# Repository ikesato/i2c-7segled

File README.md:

概要
====

- I2C を使用した7セグメントLED表示器です
- おもに Raspberry PI からの利用を想定してます  
 Raspberry PI からシェルコマンドを利用して直接制御可能
- 点滅、スクロール機能
- 最大で８つのページ切り替え機能

### パーツ

- PIC18F14K50 (SOIC)  
 1.25mm ピッチ

- TD62083 (SOIC)  
 1.25mm ピッチ

- ダイナミック接続４桁高輝度赤色７セグメントＬＥＤ表示器　カソードコモン　カソード共通接続  
 http://akizukidenshi.com/catalog/g/gI-03955/

- チップ抵抗  
 270Ω  1/4W x 8  

- チップコンデンサ  
 0.1uF  x2

### I2C通信仕様

- 通信速度 100kHz
- I2C スレーブ
- ライト要求 (Master -> Slaveへのライト要求) のみ

### コマンド

| address | data   | description |
|---------|--------|-------------|
| 0x00    | なし   | リセット    |
| 0x01    | なし   | LCD消灯     |
| 0x02    | 1..8   | 最大ページ数設定  |
| 0x03    | 0..255 | スクロール速度設定 (0.1秒 * (指定値+1)) *1  |
| 0x04    | 0..255 | ページ切り替え速度設定 (0.1秒 * (指定値+1))  |
| 0x05    | 0..255 | 点滅速度設定 (0.1秒 * (指定値+1))  |
| 0x06    | 0..1   | スクロール設定 (0:disable 1:enable)|
| 0x07    | 0..1   | 点滅設定 (0:disable 1:enable) |
| 0x10    | 0..7   | カレントページ設定 *2 |
| 0x11    | 文字列 | 描画文字列を指定、終端は 0x00 を指定します *3 |

*1 ... 文字のスクロール速度になります。例えば 19 を指定した場合 0.1*(19+1) で2秒単位にスクロールします。  
*2 ... 0 から数えるページ数を指定します。範囲は 0 から 最大ページ数-1 になります。  
*3 ... 描画文字列は ASCII コードで指定します。表示可能文字は数字、スペース、ハイフン、アンダースコア、パイプ、アルファベット（大文字、小文字）、ピリオドです。  

### 回路図

[EAGLE ファイル](./doc/eagle/i2c-7segled-SOIC.sch)

### ボード

[EAGLE ファイル](./doc/eagle/i2c-7segled-SOIC.brd)

### Unix シェルでの使用方法

shell ディレクトリにあるシェルコマンド利用することで簡単に LED を制御できます。

|コマンド              |引数  |説明                   |
|----------------------|------|-----------------------|
|7seg_clear            |なし  |7seg LCD をクリアします|
|7seg_enable_blink     |0..1  |点滅設定 (0:disable 1:enable)|
|7seg_enable_scroll    |0..1  |スクロール設定 (0:disable 1:enable)|
|7seg_puts             |文字列|描画文字列を指定|
|7seg_puts_from_stdin  |なし  |文字列を標準入力からリードして描画します。CTRL-C で中断するまで続けます。|
|7seg_reset            |なし  |リセット、内部変数ふくめ全て初期化します|
|7seg_set_blink_speed  |0..255| 点滅速度設定 (0.1秒 * (指定値+1))  |
|7seg_set_current_page |0..7  | カレントページ設定 |
|7seg_set_flip_speed   |0..255| ページ切り替え速度設定 (0.1秒 * (指定値+1))  |
|7seg_set_page_num     |1..8  | 最大ページ数設定  |
|7seg_set_scroll_speed |0..255| スクロール速度設定 (0.1秒 * (指定値+1))  |

例
```````````````````
cd shell
./7seg_reset
./7seg_enable_scroll 1
./7seg_set_scroll_speed 10
./7seg_puts "HELLO"
```````````````````

### 仕様

| 機能               | 仕様  |
|--------------------|--------------|
|インターフェース    |I2Cスレーブ   |
|I2Cスレーブアドレス|0x70         |
|I2C転送速度         |100kHz        |
|最大表示文字数      |終端NULL含めて200文字。複数ページの場合は各ページの終端NULL含めて合計で200文字|
|使用可能文字        |ASCII コードでスペース、ハイフン、アンダースコア、パイプ、アルファベット（大文字、小文字）、ピリオド|
|最大ページ数        |8ページ|
|表示機能            |ページ切り替え、文字スクロール、点滅、クリア|

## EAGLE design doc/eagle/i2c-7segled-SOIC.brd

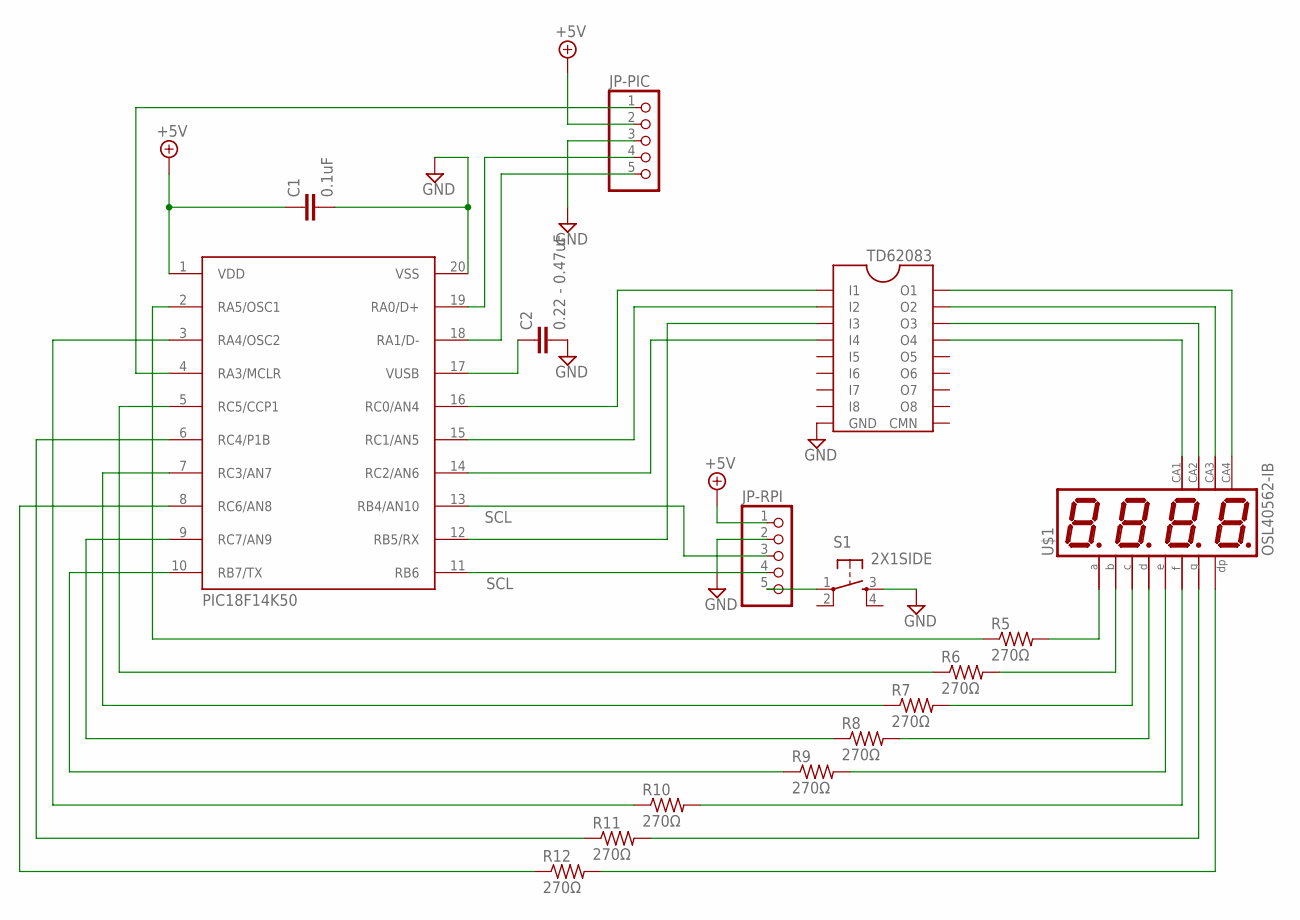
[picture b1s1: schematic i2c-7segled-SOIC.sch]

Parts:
C1: 0.1uF; C0504
C2: 0.22 - 0.47uF; C0504
JP-PIC: PINHD-1X5; 1X05
JP-RPI: PINHD-1X5; 1X05
PIC18F14K50: PIC18F14K50-SO; SO20
R5, R6, R7, R8, R9, R10, R11, R12: 270Ω; M0805
S1: 2X1SIDE
U$1: OSL40562-IB; OSL40562
U$2: TD62083; SO18

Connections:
+5V: C1.1, JP-PIC.2, JP-RPI.1, PIC18F14K50.1 (VDD)
GND: C1.2, C2.2, JP-PIC.3, JP-RPI.2, PIC18F14K50.20 (VSS), S1.3 (S), U$2.9 (GND)
unnamed: U$1.6 (CA), U$2.18 (O1)
unnamed: C2.1, PIC18F14K50.17 (VUSB)
unnamed: PIC18F14K50.12 (RB5/RX), U$2.3 (I3)
unnamed: JP-RPI.5, S1.1
unnamed: PIC18F14K50.14 (RC2/AN6), U$2.4 (I4)
unnamed: PIC18F14K50.15 (RC1/AN5), U$2.2 (I2)
unnamed: PIC18F14K50.16 (RC0/AN4), U$2.1 (I1)
unnamed: U$1.9 (CA), U$2.16 (O3)
unnamed: U$1.8 (CA), U$2.17 (O2)
unnamed: U$1.12 (CA), U$2.15 (O4)
unnamed: PIC18F14K50.2 (RA5/OSC1), R5.1
unnamed: R5.2, U$1.11 (A)
unnamed: PIC18F14K50.5 (RC5/CCP1), R6.1
unnamed: PIC18F14K50.7 (RC3/AN7), R7.1
unnamed: PIC18F14K50.9 (RC7/AN9), R8.1
unnamed: PIC18F14K50.10 (RB7/TX), R9.1
unnamed: PIC18F14K50.3 (RA4/OSC2), R10.1
unnamed: PIC18F14K50.6 (RC4/P1B), R11.1
unnamed: PIC18F14K50.8 (RC6/AN8), R12.1
unnamed: R6.2, U$1.7 (B)
unnamed: R7.2, U$1.4 (C)
unnamed: R8.2, U$1.2 (D)
unnamed: R9.2, U$1.1 (E)
unnamed: R10.2, U$1.10 (F)
unnamed: R11.2, U$1.5 (G)
unnamed: R12.2, U$1.3 (DP)
unnamed: JP-PIC.1, PIC18F14K50.4 (RA3/MCLR)
unnamed: JP-PIC.4, PIC18F14K50.19 (RA0/D+)
unnamed: JP-PIC.5, PIC18F14K50.18 (RA1/D-)
unnamed: JP-RPI.4, PIC18F14K50.11 (RB6)
SCL: JP-RPI.3, PIC18F14K50.13 (RB4/AN10)

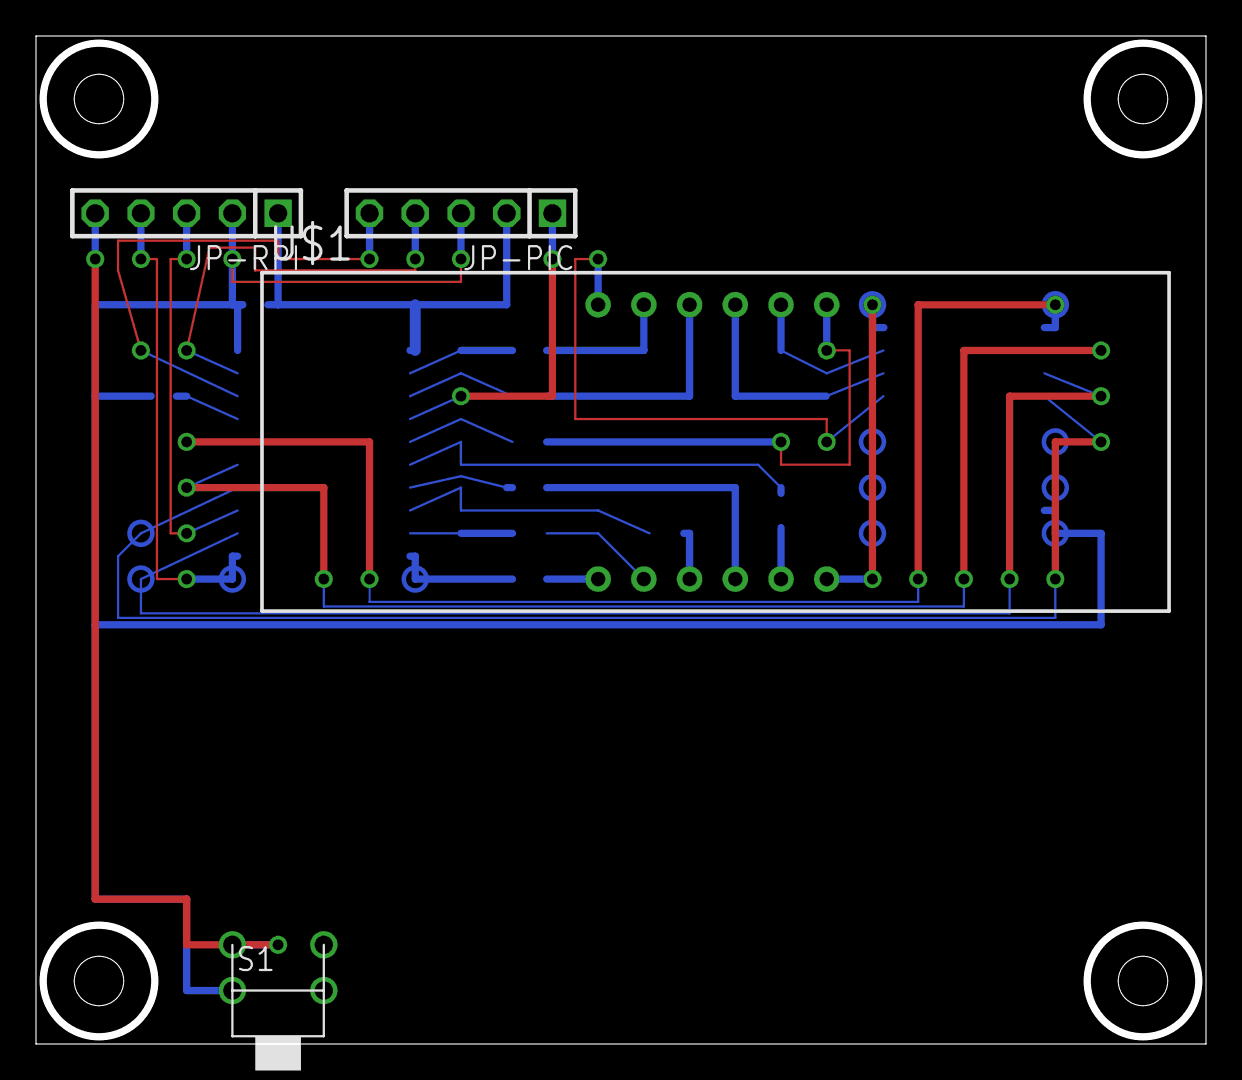
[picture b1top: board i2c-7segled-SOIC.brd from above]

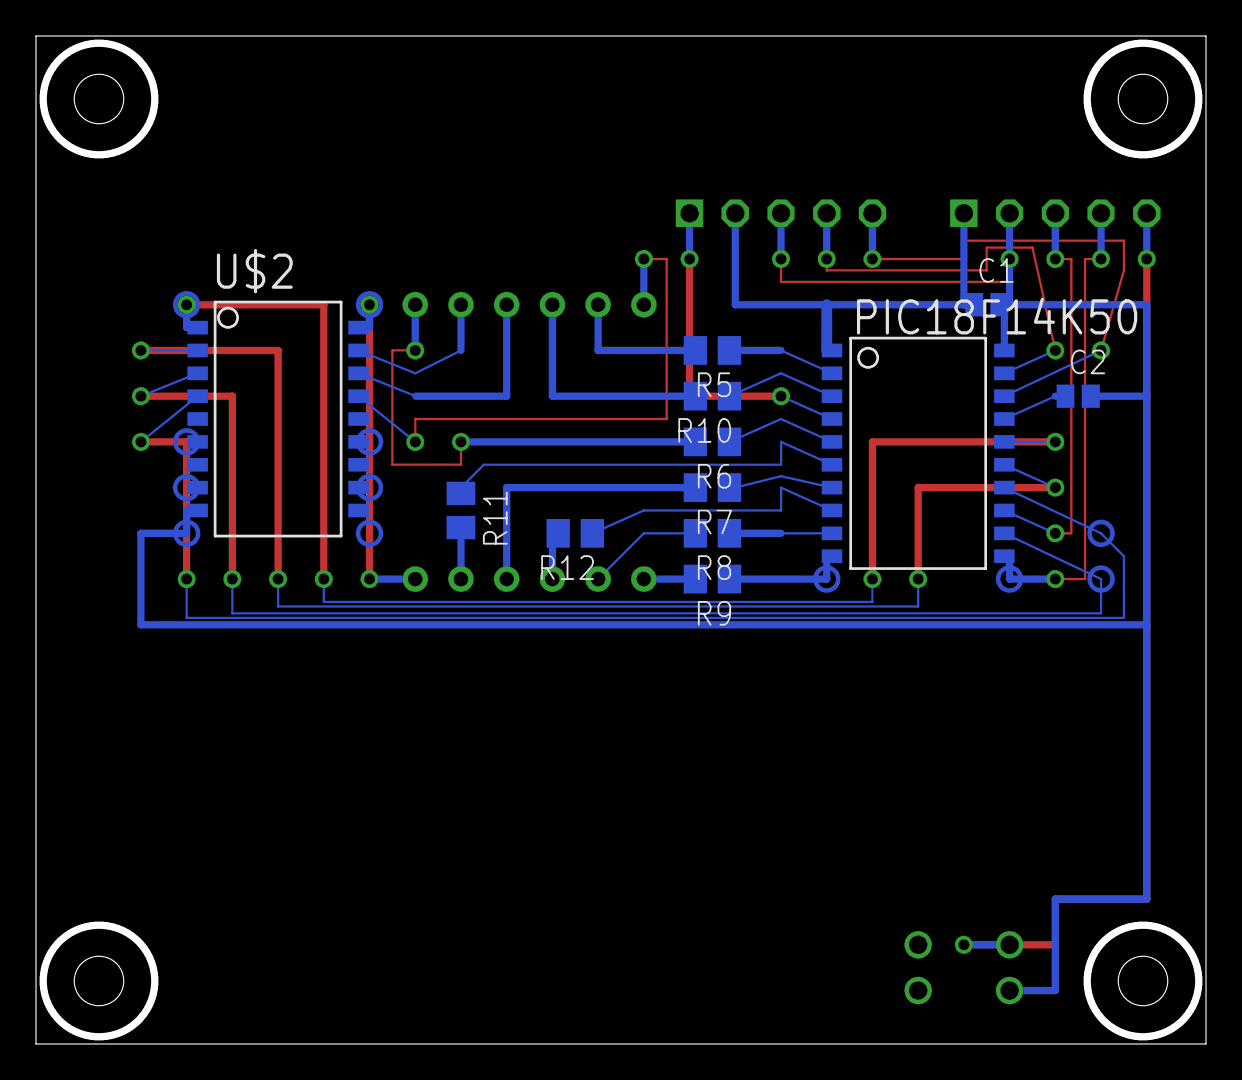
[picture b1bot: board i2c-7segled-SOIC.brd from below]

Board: 2 copper layers, 64.6 x 55.6 mm, 17 parts (12 on the bottom side), 33 nets.

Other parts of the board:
U$3: A4L-LOC

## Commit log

2015-06-02 implement digit font
2015-06-02 change indent to cc-mode only
2015-06-02 remove unnecessary comment
2015-06-02 mv README.md to root
2015-06-02 implement upper case of font
2015-06-07 implment lower case fonts
2015-06-07 modify comment
2015-06-16 implement 7 segment lcd
2015-06-16 change scroll speed
2015-06-19 implemented i2c
2015-06-19 add i2c specification
2015-06-20 fix scroll problem when page_num == 1
2015-06-20 add seg7_clear
2015-06-20 change buffer size
2015-06-20 add i2c command for clear
2015-06-20 refactoring commit. change word 'move' to 'scroll'.
2015-06-21 refactoring commit. change word 'time' to 'speed'.
2015-06-21 refactoring commit. change word 'rotate' to 'flip'.
2015-06-21 fix wrong strings pointer problem
2015-06-21 fix only period doesn't draw problem
2015-06-21 add '-', '_' and '|' characters
2015-06-21 add firmware
2015-06-21 add eagle documents
2015-06-21 Add 7seg_command
2015-06-24 remove unnecessary wires for borad documents
2015-06-28 add puts_from_stdin in 7seg_command
2015-06-28 add 7seg_puts_from_stdin
2015-06-29 add specifications
2015-06-29 update eagle documents
2015-06-29 add I2C slave address in specifications
2015-06-29 remove TODO comment
